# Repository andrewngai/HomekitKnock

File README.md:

# HomekitKnock

This repo is the resources for the project on https://youtu.be/X5Ox_uFtGn0

this device takes certain patterns of knocking and turns them into homekit triggers which you can program to automate other accessories

3D printed case: https://www.thingiverse.com/thing:4758245

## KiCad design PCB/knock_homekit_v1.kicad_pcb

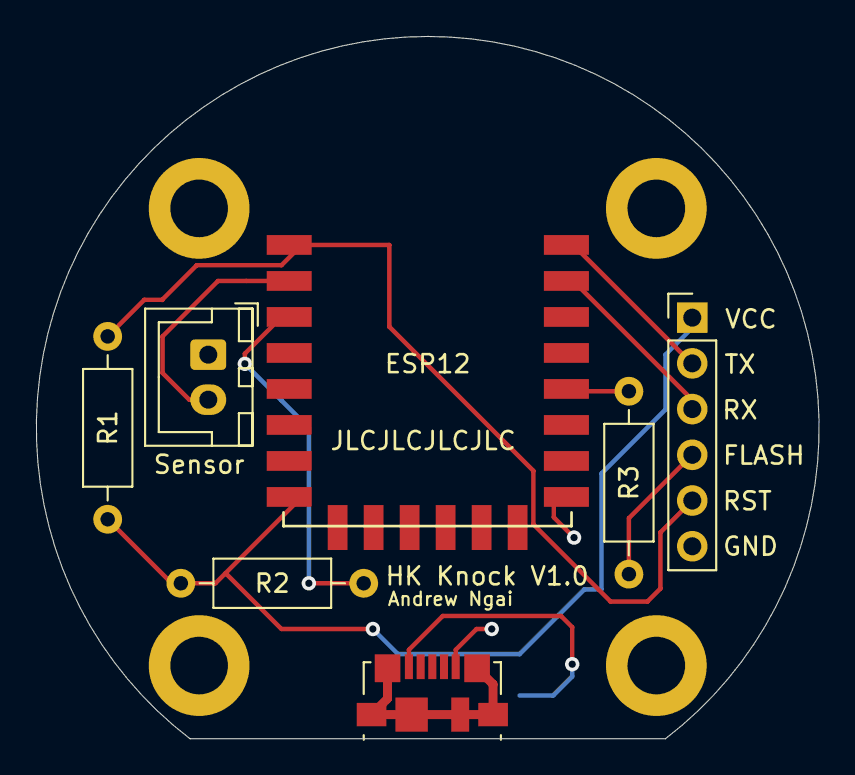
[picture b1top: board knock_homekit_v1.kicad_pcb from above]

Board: 2 copper layers, 43.5 x 39.0 mm, 8 parts (1 on the bottom side), 10 nets.

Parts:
AMS1117-3.3: AMS1117-3.3; SOT-223-3_TabPin2
ESP12: ESP-12E; ESP-12E_SMD
J3: Program; PinHeader_1x06_P2.54mm_Vertical
MicroUSB: USB_B_Micro; USB_Micro-B_Molex_47346-0001
R1, R2, R3: 10K; R_Axial_DIN0207_L6.3mm_D2.5mm_P10.16mm_Horizontal
Sensor: Sensor; JST_XH_B2B-XH-A_1x02_P2.50mm_Vertical

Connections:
GND: AMS1117-3.3.1, ESP12.9, J3.6, MicroUSB.5, Sensor.1
unnamed: AMS1117-3.3.2, ESP12.8, J3.1, R1.1, R2.2
unnamed: AMS1117-3.3.3, MicroUSB.1
unnamed: ESP12.16, J3.2
unnamed: ESP12.15, J3.3
unnamed: J3.4, R3.1
unnamed: ESP12.1, J3.5, R1.2
unnamed: ESP12.3, R2.1
unnamed: ESP12.12, R3.2
unnamed: ESP12.2, Sensor.2

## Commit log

2021-02-11 Initial upload of arduino sketch
2021-02-11 Initial upload of PCB files
